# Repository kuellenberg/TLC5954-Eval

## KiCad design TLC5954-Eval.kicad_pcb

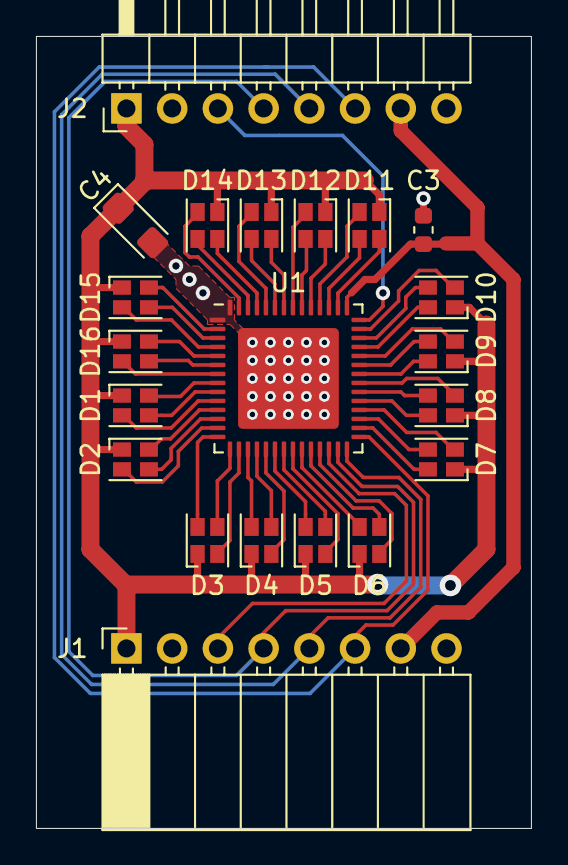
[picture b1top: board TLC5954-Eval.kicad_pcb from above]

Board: 2 copper layers, 27.5 x 44.0 mm, 21 parts (0 on the bottom side), 56 nets.

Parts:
C3: 100nF; C_0603_1608Metric
C4: 10µF; CP_EIA-3216-18_Kemet-A
D1, D2, D3, D4, D5, D6, D7, D8, D9, D10, D11, D12, D13, D14, D15, D16: LED_ARGB; LED_Cree-PLCC4_2x2mm_CW
J1: Conn_01x08; PinSocket_1x08_P2.54mm_Horizontal
J2: Conn_01x08; PinHeader_1x08_P2.54mm_Horizontal
U1: TLC5954; QFN-56-1EP_8x8mm_P0.5mm_EP5.6x5.6mm

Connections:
+3V3: C3.1, J1.7, J2.7, U1.43
/B0: D1.4, U1.10
/B1: D2.4, U1.13
/B2: D3.4, U1.16
/B3: D4.4, U1.19
/B4: D5.4, U1.22
/B5: D6.4, U1.25
/B6: D7.4, U1.32
/B7: D8.4, U1.35
/B8: D9.4, U1.38
/B9: D10.4, U1.41
/B10: D11.4, U1.46
/B11: D12.4, U1.49
/B12: D13.4, U1.52
/B13: D14.4, U1.55
/B14: D15.4, U1.4
/B15: D16.4, U1.7
/BLANK: J1.6, J2.6, U1.29
/G0: D1.3, U1.9
/G1: D2.3, U1.12
/G2: D3.3, U1.15
/G3: D4.3, U1.18
/G4: D5.3, U1.21
/G5: D6.3, U1.24
/G6: D7.3, U1.31
/G7: D8.3, U1.34
/G8: D9.3, U1.37
/G9: D10.3, U1.40
/G10: D11.3, U1.45
/G11: D12.3, U1.48
/G12: D13.3, U1.51
/G13: D14.3, U1.54
/G14: D15.3, U1.3
/G15: D16.3, U1.6
/LAT: J1.4, J2.4, U1.27
/R0: D1.2, U1.8
/R1: D2.2, U1.11
/R2: D3.2, U1.14
/R3: D4.2, U1.17
/R4: D5.2, U1.20
/R5: D6.2, U1.23
/R6: D7.2, U1.30
/R7: D8.2, U1.33
/R8: D9.2, U1.36
/R9: D10.2, U1.39
/R10: D11.2, U1.44
/R11: D12.2, U1.47
/R12: D13.2, U1.50
/R13: D14.2, U1.53
/R14: D15.2, U1.2
/R15: D16.2, U1.5
/SCLK: J1.5, J2.5, U1.28
/SIN: J1.3, U1.26
/SOUT: J2.3, U1.42
GND: C3.2, C4.2, J1.2, J1.8, J2.2, J2.8, U1.1, U1.56, U1.57
VCC: C4.1, D1.1, D2.1, D3.1, D4.1, D5.1, D6.1, D7.1, D8.1, D9.1, D10.1, D11.1, D12.1, D13.1, D14.1, D15.1, D16.1, J1.1, J2.1
